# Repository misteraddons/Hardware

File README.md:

# Hardware
PCBs for various add-ons and accessories

SNES2HDMI: Used for BlissBox cables - not compatible with LLOAD

SNES2DB15: Used for LLOAD

USB 3 Breakout: USB 3 connector to JST-XH-10 useful for interfacing MiSTer's IO Board User-IO port

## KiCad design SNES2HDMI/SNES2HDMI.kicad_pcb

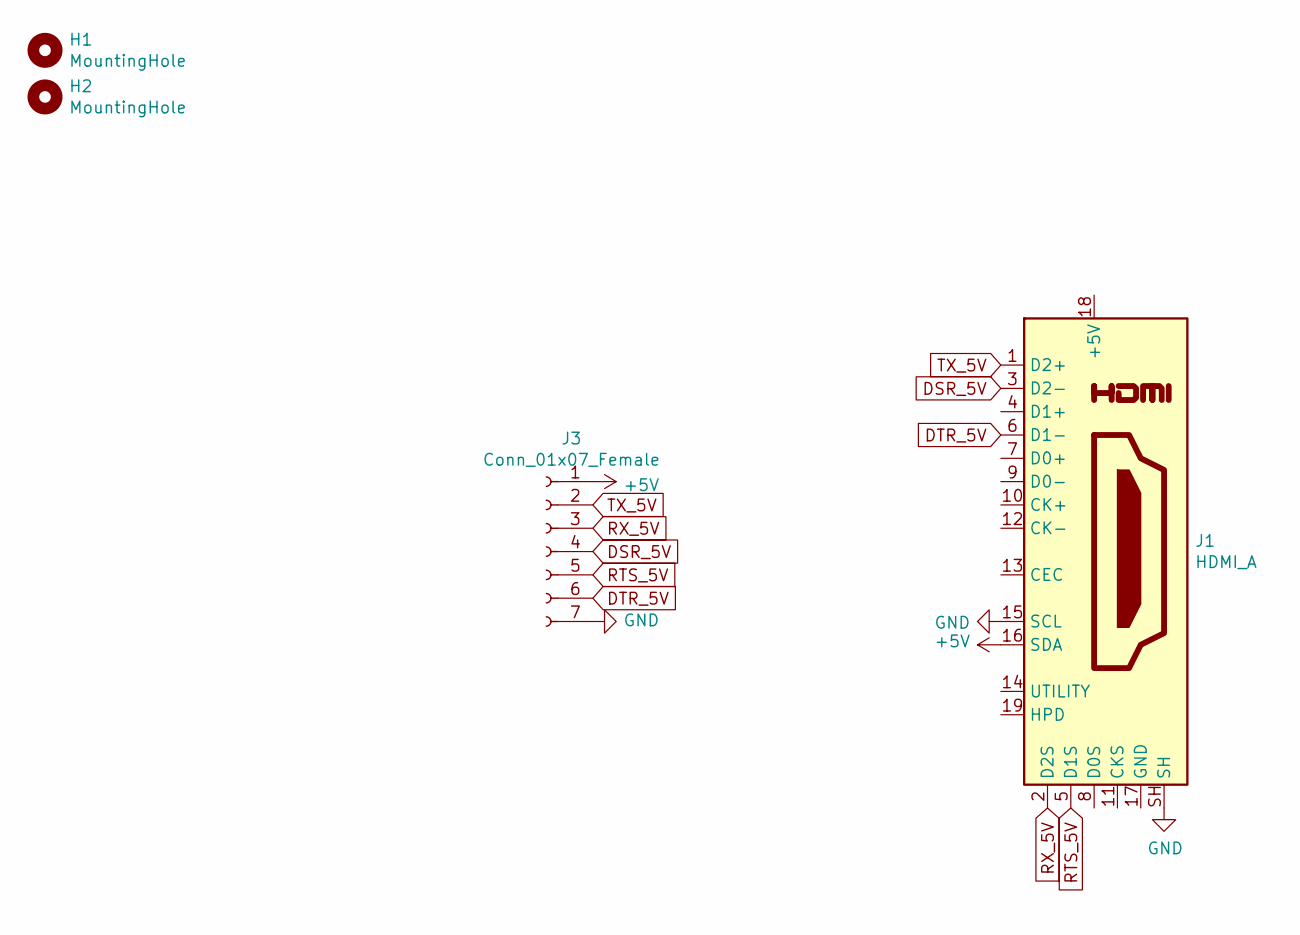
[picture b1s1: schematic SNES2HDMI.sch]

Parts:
H1, H2: MountingHole; MountingHole_3mm_Pad
J1: HDMI_A; HDMI
J3: Conn_01x07_Female; SNES_Controller

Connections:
+5V: J1.16 (SDA), J3.1
DSR_5V: J1.3 (D2-), J3.4
DTR_5V: J1.6 (D1-), J3.6
GND: J1.15 (SCL), J1.SH, J3.7
RTS_5V: J1.5 (D1S), J3.5
RX_5V: J1.2 (D2S), J3.3
TX_5V: J1.1 (D2+), J3.2

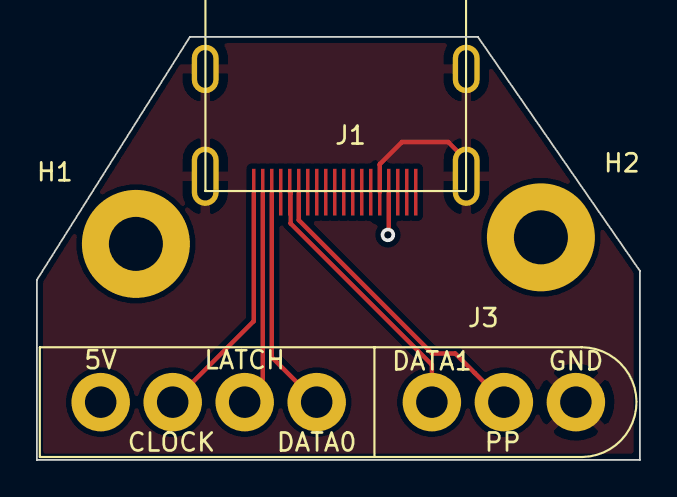
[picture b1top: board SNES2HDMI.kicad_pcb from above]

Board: 2 copper layers, 33.5 x 23.5 mm, 4 parts (0 on the bottom side), 7 nets.

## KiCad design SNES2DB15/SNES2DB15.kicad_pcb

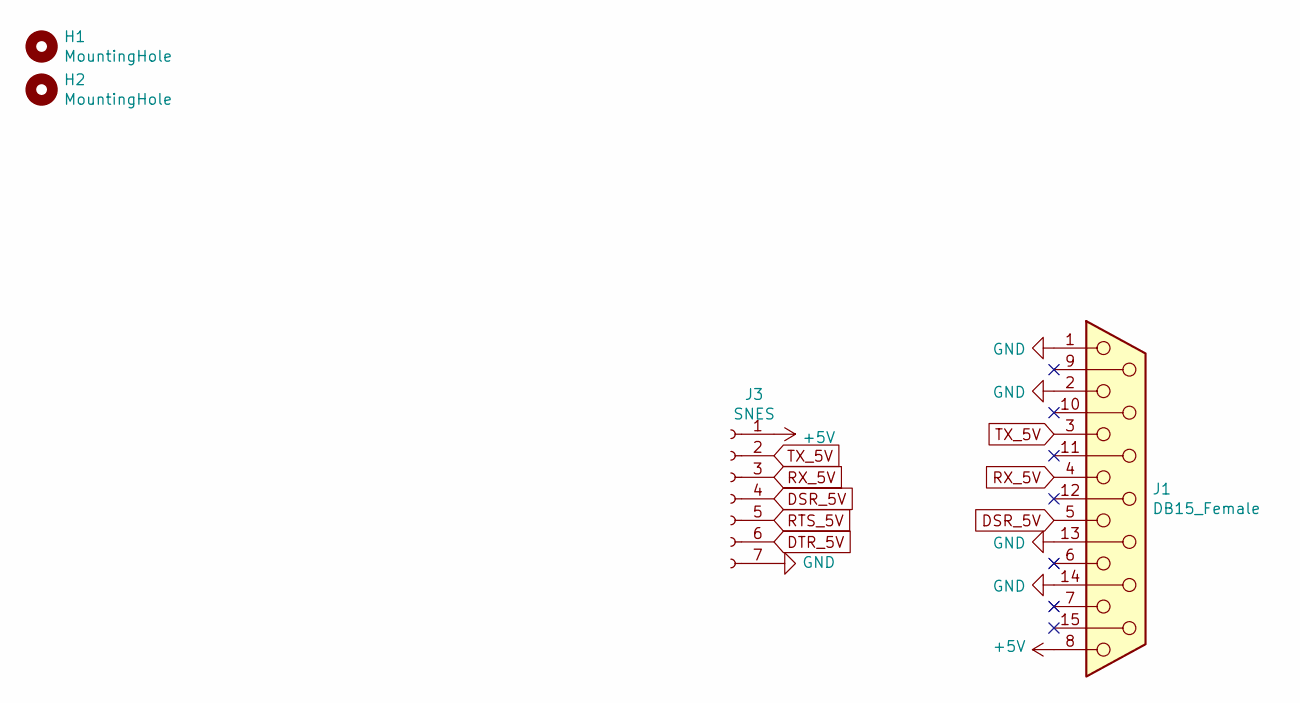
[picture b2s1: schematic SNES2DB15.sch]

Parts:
H1, H2: MountingHole; MountingHole_3mm_Pad
J1: DB15_Female; DSUB-15_Female_Horizontal_P2.77x2.84mm_EdgePinOffset7.70mm_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
J3: SNES; SNES_Controller

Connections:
+5V: J1.8, J3.1
DSR_5V: J1.5, J3.4
DTR_5V: J3.6
GND: J1.1, J1.2, J1.13, J1.14, J3.7
RTS_5V: J3.5
RX_5V: J1.4, J3.3
TX_5V: J1.3, J3.2

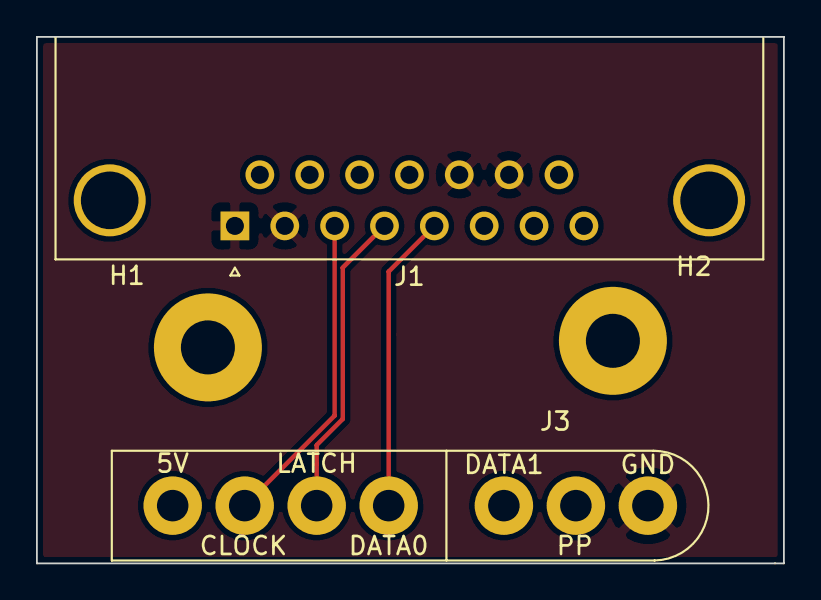
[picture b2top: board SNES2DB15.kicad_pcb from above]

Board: 2 copper layers, 41.5 x 29.2 mm, 4 parts (0 on the bottom side), 5 nets.

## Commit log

2019-12-07 SNES adapters for BlisSTer cables and LLOAD
2019-12-07 USB3Breakout board
